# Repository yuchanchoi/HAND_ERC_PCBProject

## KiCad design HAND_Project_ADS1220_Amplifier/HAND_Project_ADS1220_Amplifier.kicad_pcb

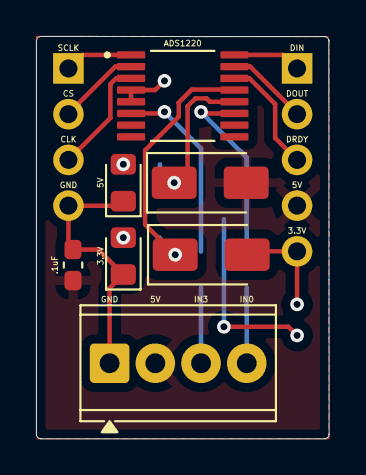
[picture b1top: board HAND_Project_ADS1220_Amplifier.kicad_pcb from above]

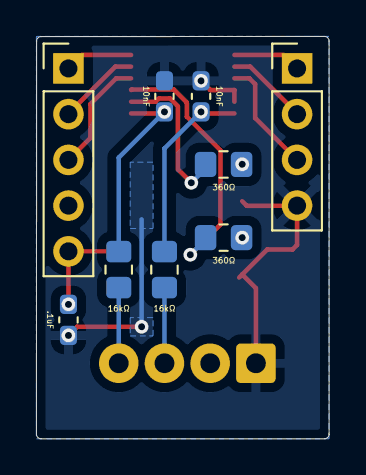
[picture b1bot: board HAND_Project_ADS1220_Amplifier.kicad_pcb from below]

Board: 2 copper layers, 16.3 x 22.4 mm, 16 parts (9 on the bottom side), 17 nets.

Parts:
3.3V, 5V: LED; LED_0805_2012Metric_Pad1.15x1.40mm_HandSolder
10nF, 10nF#2: 10nF; C_0603_1608Metric_Pad1.08x0.95mm_HandSolder
16kΩ, 16kΩ#2: 16k; R_0805_2012Metric_Pad1.20x1.40mm_HandSolder
360Ω, 360Ω#2: 360; R_0805_2012Metric_Pad1.20x1.40mm_HandSolder
.1uF, .1uF#2: .1 uF; C_0603_1608Metric_Pad1.08x0.95mm_HandSolder
D1, D2: SS12; D_SMA
GND: Screw_Terminal_01x04; TerminalBlock_Phoenix_MPT-0,5-4-2.54_1x04_P2.54mm_Horizontal
J2: Conn_01x05_Pin; PinHeader_1x05_P2.54mm_Vertical
J7: Conn_01x04_Pin; PinHeader_1x04_P2.54mm_Vertical
U1: ADS1220IPWR; SOP65P640X120-16N

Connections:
3.3V: .1uF#2.1, D1.2 (A), J2.5
5V: .1uF.1, D2.2 (A), GND.2, J2.4
/AIN0: 10nF.1, 16kΩ.2, U1.11 (AIN0/REFP1)
/AIN3: 10nF#2.1, 16kΩ#2.2, U1.6 (AIN3/REFN1)
/AVDD: 360Ω#2.1, D2.1 (K), U1.12 (AVDD)
/CLK: J7.3, U1.3 (CLK)
/CS: J7.2, U1.2 (~CS)
/DIN: J2.1, U1.16 (DIN)
/DOUT: J2.2, U1.15 (DOUT/~DRDY)
/DRDY: J2.3, U1.14 (~DRDY)
/DVDD: 360Ω.1, D1.1 (K), U1.13 (DVDD)
/SCLK: J7.1, U1.1 (SCLK)
GND: 3.3V.1 (K), 5V.1 (K), 10nF.2, 10nF#2.2, .1uF.2, .1uF#2.2, GND.1, J7.4, U1.4 (DGND), U1.5 (AVSS)
unnamed: 3.3V.2 (A), 360Ω.2
unnamed: 5V.2 (A), 360Ω#2.2
unnamed: 16kΩ#2.1, GND.3
unnamed: 16kΩ.1, GND.4

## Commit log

2026-02-05 Changes Feb 5th, 2026
    Added com_ports.py to the .src file
    Minimal non-function related changes to some code
2026-02-07 Changes Feb 6th, 2026
    - Not any real changes to code
    - Load Cell Mount Prototype (.step and .3mf g code file with custom infill for heated threaded insert)
2026-02-08 Feb 8th Updates
    - Code changed to contain initial calibration attempt
    - main.cpp and loadcell.liveplot.py code changed to have option to either liveplot or read via serial monitor (with input time) depending on which blocks/sections of code you comment out on both scri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
    - New loadcell mount design (need to create new loadcell design that will support bigger calibration weight sets
2026-02-09 Updated code
    Updated the code for easier calibration setup!
    Now you can run the code and have multiple tests done in one go.
2026-02-10 Code Update
    The error calculation has been updated to account for negative values as well."
    new negative strain slope value after 2nd round of testing
2026-02-10 Feb 10th Code Major Changes
    This code is the first prototype for the final calibration.
    This code now fixes the big initial offset value issues by dynamically changing the strain offset by taking the average of the first 80 values and using that as the offset (this means that the loadce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
2026-02-26 kicad stuff
    a
2026-02-26 KiCad
    need to assign footprints
2026-03-05 Finished schematics + footprints
    Need to work on actual PCB design
2026-03-05 pin? idk
    stuff
2026-03-05 After meeting
2026-03-05 4 PM meeting
    stuff
2026-03-06 Added Pin and Decoupling Capacitors + Fixed PCB version issue
    PCB version was a bit messed up because Yuchan and I merged 2 of them together. Have to work on this project at different times if working remotely.
2026-03-12 Attempted to trace PCB... became very confused
    Attempting to trace PCB was very difficult. I think I may need to use more vias and perhaps the underside of the board as well because my components are surface mounted.
2026-04-08 Components Update
    Update 1: 2x LPF RC filters added for both Analog Signals from the J1 screw into the ADS
    Update 2: 1x Power Connector pin for 5V and GND added as suggested by Luke
2026-04-14 Eric's PCB (without teensy integration)
2026-04-15 Finished Organizing and Sectioning schematic
2026-04-16 Finished Design of PCB without teensy integration
    Added external power supply, changed mounting holes to M3, generated gerber files, and the cost to manufacture 3 PCBs is $8.95
2026-04-17 Final touches
    matched footprints with yuchan's PCB
2026-04-20 zip of no_teensy board
2026-04-29 Tried to implement ADS1220 chip.
    Failed.
2026-04-29 Got the ADS1220 chip to work
2026-05-06 Yuchan - Changes to code (Slight) - May 6th, 2026
    Made slight edits to the main.cpp, loadcell_liveplot codes:
    main.cpp;
    - Edited so that the code outputs the format expected for loadcell_liveplot
    loadcell_liveplot.py:
    - Added
    ```
2026-05-27 no_teensy_PCB
2026-05-28 new PCB no teensy
2026-05-29 Finished new PCB without teensy integration
